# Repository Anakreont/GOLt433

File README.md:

# GOLt433 - 433 MHz LoRa APRS balloon tracker with a camera

Board name on the PCB and in the files: **T433 lite**.

Sends position as a normal LoRa APRS frame on 433.775 MHz (SF12, BW 125 kHz) and photos as SSDV packets in APRS
"user-defined" frames (`{{I` + base91, the Pecan Pico format), so LoRa APRS iGates can pass them to APRS-IS.

**Status (2026-11-23): five v1.0 boards built by JLCPCB. Radio, GPS and camera work on the bench. Never flown, never tested
through a public iGate.**

## Hardware v1.0 (`pcb_lite/`)
- ESP32-S3-MINI-1U-N4R2, E22-400MM22S (SX1268, **crystal, not TCXO**), ATGM336H, OV2640 on a 24-pin FPC connector,
  ME6211C33 LDO, camera LDOs switched by a GPIO. 2 layers, everything on top, 32 x 40.6 mm, break-off PROG tab.
- Measured mass: 5.2 g without antennas, camera and solar cells.
- `kicad/` - KiCad 7 board; `jlcpcb/` - Gerbers, BOM, CPL; the Python/shell scripts are the generator used to build and route the board.
- Drawings in `img/` (Polish): USB cable on the PROG tab, where to solder antennas and cells, the FFC workaround.

### Camera connector J1 - top contact
J1 in the BOM is **AFC07-S24ECA-00 (LCSC C262643, top contact)**: the camera goes in lens down, contacts up.
The first five boards were built with a bottom-contact connector, which mirrors the pin order (camera pin 1 on pad 24):
the camera gets hot and does not work. That part has been removed from the BOM. If you have such a board, use an
FFC 24-pin 0.5 mm coupler plus a **type B** ribbon with the camera turned over (`img/T433_tasma_typ_B.png`).
- The footprint on the board is still the one drawn for the old connector. The signal pads are identical; the mounting
  tabs of the new part land on the existing pads, which are smaller than the tabs.
- The new body is about 1.5 mm longer: 0.1-0.4 mm from U7 and about 0.3 mm over the board edge. Check the placement preview.
- **A board with this connector has not been built yet.** A corrected layout (connector moved and rotated) is planned.

Other notes: the E22 crystal drifts about 40 Hz/s during the first seconds of transmission, so the first SF12 frames after
a cold start are lost (firmware sends warm-up frames). A module with a TCXO would be better.

## Firmware (`firmware/`)
- `tracker433_lite_v0_6/` - tracker. 640x480 photo, position frame repeated during the photo, warm-up frames,
  **photo resume after a power dropout** (JPEG and progress kept in LittleFS), waiting for sun when the panel voltage sags,
  position hidden below `POZYCJA_MIN_WYS_M` (only the 4-character locator is sent near the ground).
  Warm-up and resume were confirmed on hardware with v0.4/v0.5; **v0.6 itself is compiled only.**
- `tracker433_lite_rx_v0_1/` - a second T433 board as a USB receiver (prints every frame as a `T433RX;...` line).
- `hw_tests/` - bench test sketches (frames at different power, cold start, camera connector lines).
- Build: Arduino core esp32 3.0.7, board "ESP32S3 Dev Module", PSRAM enabled, Flash 4 MB, USB CDC On Boot enabled,
  RadioLib 7.1.2, TinyGPSPlus 1.1.0:
  `arduino-cli compile --fqbn "esp32:esp32:esp32s3:PSRAM=enabled,FlashSize=4M,CDCOnBoot=cdc,PartitionScheme=default" tracker433_lite_v0_6`
- Set `ZNAK` and `SSDV_ZNAK` in `config.h` to your callsign first.
- Flashing: USB on the PROG tab (V+ through a diode); first time hold B0 to ground at power-up; then upload with arduino-cli or esptool (no prebuilt images here, they would carry a callsign).

## PC receiver (`receiver_pc/`)
`t433_usb_odbior_v0_5.py` (needs `pyserial`) reads the receiver board over USB, shows frames and assembles photos.
It needs an SSDV decoder next to it: build `ssdv_dek_windows.c` with `ssdv.c` and `rs8.c` from the tracker folder.

## Not tested at all
Position frame from a real fix above 1000 m, waiting for sun, Zener protection with 8 cells, the path through public iGates and APRS-IS.

## Callsigns
`N0CALL` in the code is a placeholder. Set your own callsign before transmitting; an amateur licence is required.

## Related
GOLr20, the HF FT8/WSPR tracker with a receiver from the same author: https://github.com/Anakreont/GOLr20

## Licence
GPL-3.0 for the whole repository (see `LICENSE`). The firmware and the PC receiver include SSDV, Reed-Solomon and base91
code from Pecan Pico 9 by Philip Heron (GPL v3). Design by SQ9GOL. Source comments and drawings are in Polish.

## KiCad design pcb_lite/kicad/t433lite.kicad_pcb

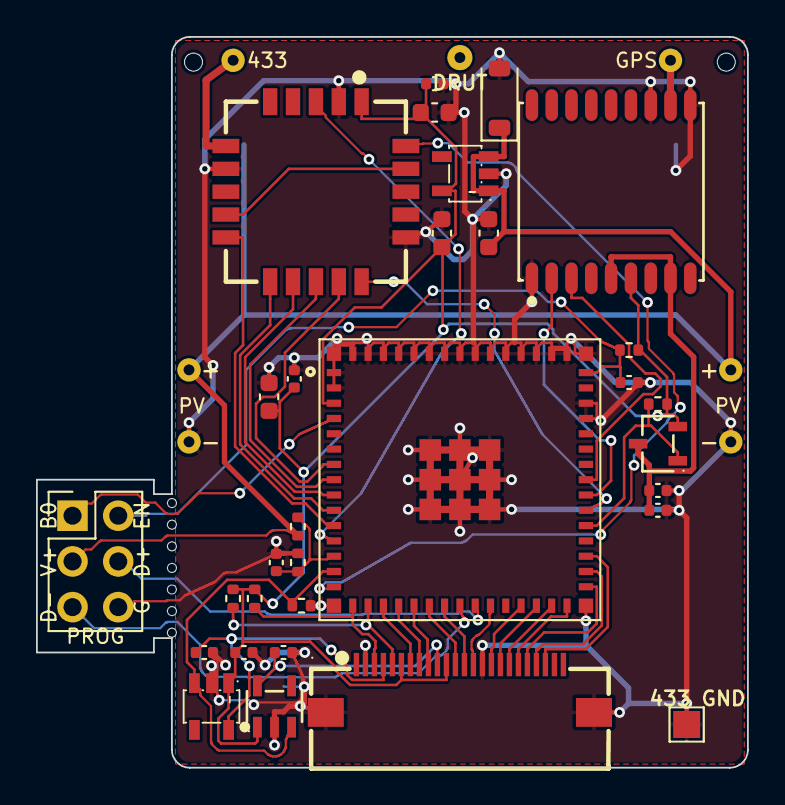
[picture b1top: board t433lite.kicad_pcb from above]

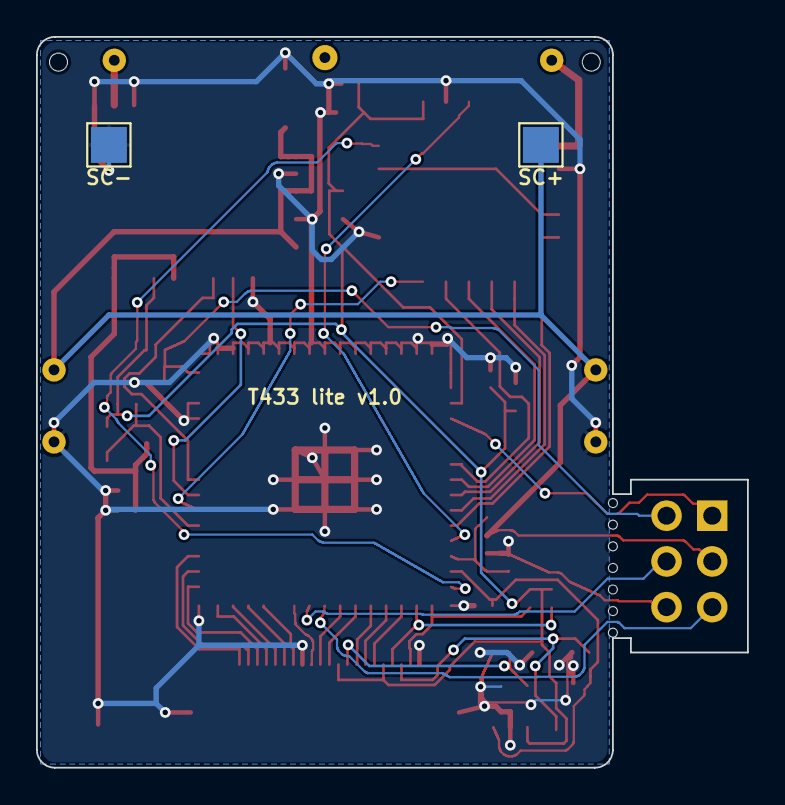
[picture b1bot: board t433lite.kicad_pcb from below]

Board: 2 copper layers, 39.5 x 40.6 mm, 49 parts (2 on the bottom side), 41 nets.

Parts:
C1, C25, C30, C31: 10uF; C_0603_1608Metric
C2, C11, C23, C26: 100nF; C_0402_1005Metric
C8, C17, C18, C19, C22: 1uF; C_0402_1005Metric
D2: BZT52C5V1 (ogr. 5,1 V); D_SOD-123
H1, H2, H3: (no value)
J1: AFC01-S24FCA-00 (OV2640); FPC24_AFC01-S24FCA
J2: PROG 2x3; PinHeader_2x03_P2.54mm_Vertical
MB1, MB2, MB3, MB4, MB5, MB6, MB7: (no value)
Q2: SI2301CDS (zas. GPS); SI2301_SOT23
R1: 10k; R_0402_1005Metric
R3, R4: 1M; R_0402_1005Metric
R10, R16: 100k; R_0402_1005Metric
R12, R13: 4.7k; R_0402_1005Metric
TP1, TP2, TP3, TP4, TP20, TP22: (no value)
TP23: 433 GND; TestPoint_Pad_1.5x1.5mm
TP24: SC+; TestPoint_Pad_2.0x2.0mm
TP25: SC-; TestPoint_Pad_2.0x2.0mm
U1: ESP32-S3-MINI-1U-N4R2; ESP32-S3-MINI-1U
U2: E22-400MM22S
U3: ATGM336H-5N31; ATGM336H
U4: ME6211C33M5G-N (3,3V); ME6211_SOT23-5
U6: ME6211C28M5G (AVDD 2,8V); ME6211_SOT23-5
U7: ME6211C12M5G (DVDD 1,2V); ME6211_SOT23-5b

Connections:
+3V3: C1.1, C2.1, C18.1, C25.1, C26.1, C31.1, J1.6, J1.11, Q2.2, R1.2, R12.2, R13.2, R16.2, U1.3, U2.1, U3.6, U4.5, U6.1, U7.1
BOOT: J2.1, U1.4
CAM_1V2: C19.1, J1.10, U7.5
CAM_2V8: C17.1, J1.4, U6.5
CAM_EN: R10.1, U1.14, U6.3, U7.3
CAM_HREF: J1.9, U1.20
CAM_PCLK: J1.17, U1.28
CAM_PWDN: J1.8, U1.19
CAM_SIOC: J1.5, R13.1, U1.17
CAM_SIOD: J1.3, R12.1, U1.16
CAM_VSYNC: J1.7, U1.18
CAM_XCLK: J1.13, U1.22
CAM_Y2: J1.19, U1.30
CAM_Y3: J1.21, U1.32
CAM_Y4: J1.22, U1.33
CAM_Y5: J1.20, U1.31
CAM_Y6: J1.18, U1.29
CAM_Y7: J1.16, U1.27
CAM_Y8: J1.14, U1.25
CAM_Y9: J1.12, U1.21
CHIP_PU: C8.1, J2.2, R1.1, U1.45
GND: C1.2, C2.2, C8.2, C11.2, C17.2, C18.2, C19.2, C22.2, C23.2, C25.2, C26.2, C30.2, C31.2, D2.2, J1.2, J1.15, J1.25, J1.26, J2.6, R4.2, R10.2, TP2.1, TP4.1, TP23.1, TP25.1, U1.1, U1.2, U1.42, U1.43, U1.46, U1.47, U1.48, U1.49, U1.50, U1.51, U1.52, U1.53, U1.54, U1.55, U1.56, U1.57, U1.58, U1.59, U1.60, U1.61, U1.62, U1.63, U1.64, U1.65, U2.2, U2.7, U2.16, U3.1, U3.10, U3.12, U4.2, U6.2, U7.2
GPS_ANT: TP20.1, U3.11
GPS_EN_N: Q2.1, R16.1, U1.35
GPS_RXD: U1.38, U3.3
GPS_TXD: U1.37, U3.2
GPS_VCC: C22.1, C23.1, Q2.3, U3.5, U3.8
LORA_ANT: TP22.1, U2.6
LORA_BUSY: U1.10, U2.11
LORA_DIO1: U1.15, U2.20
LORA_DIO2: U2.9, U2.19
LORA_MISO: U1.9, U2.12
LORA_MOSI: U1.8, U2.13
LORA_NRST: U1.12, U2.3
LORA_NSS: U1.7, U2.14
LORA_RXEN: U1.11, U2.10
LORA_SCK: U1.36, U2.15
USB_DN: J2.5, U1.23
USB_DP: J2.4, U1.24
VSC: C30.1, D2.1, J2.3, R3.1, TP1.1, TP3.1, TP24.1, U4.1, U4.3
VSC_ADC: C11.1, R3.2, R4.1, U1.13

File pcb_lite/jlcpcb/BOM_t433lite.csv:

Comment,Designator,Footprint,LCSC Part #
10uF,"C1,C25,C30,C31",C_0603_1608Metric,C19702
100nF,"C11,C2,C23,C26",C_0402_1005Metric,C1525
1uF,"C17,C18,C19,C22,C8",C_0402_1005Metric,C52923
BZT52C5V1,D2,D_SOD-123,C173407
AFC01-S24FCA-00,J1,FPC24_AFC01-S24FCA,C262669
SI2301CDS,Q2,SI2301_SOT23,C10487
10k,R1,R_0402_1005Metric,C25744
100k,"R10,R16",R_0402_1005Metric,C25741
4.7k,"R12,R13",R_0402_1005Metric,C25900
1M,"R3,R4",R_0402_1005Metric,C26083
ESP32-S3-MINI-1U-N4R2,U1,ESP32-S3-MINI-1U,C22356044
E22-400MM22S,U2,E22-400MM22S,C5333984
ATGM336H-5N31,U3,ATGM336H,C90770
ME6211C33M5G-N,U4,ME6211_SOT23-5,C82942
ME6211C28M5G,U6,ME6211_SOT23-5,C53099
ME6211C12M5G,U7,ME6211_SOT23-5b,C236672

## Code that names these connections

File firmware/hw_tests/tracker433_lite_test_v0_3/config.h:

// T433 - tracker 433 MHz z kamera, konfiguracja
// Plytka T433 v2.3 (ESP32-S3FH4R2, E22-400MM22S / SX1268, ATGM336H, OV2640)
#pragma once

// ---------- znak i APRS ----------
#define ZNAK            "N0CALL"      // znak obowiazkowy (pasmo amatorskie 70 cm)
#define SSID            11
#define APRS_DEST       "APZ433"      // APZxxx = oprogramowanie eksperymentalne
#define APRS_PATH       ""            // bez WIDE1-1 - balon slyszy wiele bramek naraz, nie zasmiecamy sieci
#define SSDV_ZNAK       "N0CALL"      // znak w naglowku SSDV (max 6 znakow)

// ---------- LoRa APRS (publicznie, EU: 433,775 MHz SF12 BW125 CR4/5) ----------
#define APRS_FREQ       433.775
#define APRS_SF         12
#define APRS_BW         125.0
#define APRS_CR         5
#define LORA_MOC_DBM    17            // 50 mW; E22 max 22 dBm (wiecej pradu z paneli)
#define LORA_TCXO_V     1.8           // E22-400MM22S ma TCXO zasilane z DIO3 (1,8 V); 0 = kwarc
#define LORA_SYNC       0x12          // LoRa APRS uzywa "private" sync word 0x12

// ---------- ramka prywatna z dokladna pozycja (tylko nasze odbiorniki) ----------
#define PRYW_WLACZ      1
#define PRYW_FREQ       434.500       // do ustalenia z planem pasma
#define PRYW_SF         10
#define PRYW_BW         125.0
#define PRYW_CR         5

// ---------- harmonogram ----------
#define CYKL_S              600       // co ile sekund nowy cykl (status + pozycja + zdjecie)
#define GPS_FIX_TIMEOUT_S   180       // max czekanie na fix GPS w cyklu
#define PRZERWA_PAKIET_MS   1500      // przerwa miedzy pakietami zdjecia
#define STATUS_CO_PAKIETOW  20        // status APRS (bez pozycji) co tyle pakietow zdjecia

// ---------- kamera / zdjecie ----------
#define FOTO_ROZM       FRAMESIZE_QVGA   // 320x240 (SSDV: wymiary wielokrotnoscia 16)
#define FOTO_JAKOSC     40               // jakosc JPEG 0-100 (mniej = mniej pakietow)
#define SSDV_JAKOSC     4                // jakosc SSDV 0-7 (przekodowanie w SSDV)
#define NAPIS_SKALA     2                // powiekszenie czcionki 5x7 na zdjeciu
#define NAPIS_DOL       1                // powtorz pasek z pozycja na dole zdjecia

// ---------- zasilanie ----------
#define VSC_MIN_FOTO    3.60             // ponizej: bez zdjecia (tylko status + pozycja)
#define VSC_MIN_NADAJ   3.30             // ponizej: nic nie nadawaj, uspij
#define VSC_DZIELNIK    2.0              // R3/R4 1M/1M

// ---------- piny (mapa GPIO plytki T433 lite v1.0, modul ESP32-S3-MINI-1U-N4R2) ----------
#define PIN_LORA_DIO1   11    // v1.0 po poprawce 9.11 (bylo IO1)
#define PIN_LORA_SCK    40    // v1.0 po poprawce 9.11 (bylo IO2)
#define PIN_LORA_NSS    3
#define PIN_LORA_MOSI   4
#define PIN_LORA_MISO   5
#define PIN_LORA_BUSY   6
#define PIN_LORA_RXEN   7
#define PIN_LORA_NRST   8
#define PIN_VSC_ADC     9     // ADC1_CH8, dzielnik 1M/1M
#define PIN_CAM_EN      10    // stan wysoki = LDO kamery 2,8 V i 1,2 V wlaczone (R10 100k do masy)
#define PIN_GPS_EN_N    39    // stan niski = GPS wlaczony (Q2 SI2301, R16 100k do 3,3 V)
#define PIN_GPS_RX      41    // ESP RX  <- TXD GPS
#define PIN_GPS_TX      42    // ESP TX  -> RXD GPS
#define CAM_SIOD        12
#define CAM_SIOC        13
#define CAM_VSYNC       14
#define CAM_PWDN        15
#define CAM_HREF        16
#define CAM_Y9          17
#define CAM_XCLK        18
#define CAM_Y8          21
#define CAM_Y7          47
#define CAM_PCLK        33
#define CAM_Y6          34
#define CAM_Y2          48
#define CAM_Y5          35
#define CAM_Y3          36
#define CAM_Y4          37
